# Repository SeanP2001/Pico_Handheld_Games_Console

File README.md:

# Pico Handheld Games Console

## Table of Contents

* [Introduction](#introduction)
* [Brief](#brief)
* [Circuitry](#circuitry)
  + [Schematic](#schematic)
  + [PCB Design](#pcb-design)
  + [Display Pinout Jumpers](#display-pinout-jumpers)
  + [Soldered PCB](#soldered-pcb)
* [Board Manager & Programming Setup](#board-manager---programming-setup)
* [Code](#code)
* [Enclosure](#enclosure)
  + [CAD Renders](#cad-renders)
  + [3D Printed and Assembled](#3d-printed-and-assembled)
* [Game Library](#game-library)
* [Further Work](#further-work)

## Introduction

I started this project to follow on from my [ATtiny Handheld Games Console](https://github.com/SeanP2001/ATtiny_Handheld_Games_Console). I decided the project was not as accessible as I wanted because programming an ATtiny is not simple enough for a beginner. While the limitations of the ATtiny make it a fun challenge to create games, it would be nice to be able to make something more elaborate.

## Brief

I wanted to make a USB-programmable games console which could be programmed using either MicroPython or C++ (Arduino). I also wanted to use silicone button membranes to give the buttons a more premium feel compared to the tactile buttons on the ATtiny console. I also decided to make a version with a colour LCD display (see the ["LCD_Version"](https://github.com/SeanP2001/Pico_Handheld_Games_Console/tree/LCD_Version) branch).

## Circuitry

### Schematic

### PCB Design

|  |  |
| ------------------------------------ | ----------------------------------- |

### Display Pinout Jumpers

A feature of the PCB is the jumper connections under the display. The I2C OLED displays do not all have the same pin layout. When you buy a display online, the item you receive may not have the same pinout as the one in the photos. Due to this inconsistency, I designed the board to work with both pinouts. If your display has the pinout (in order) Vcc/GND/SCL/SDA then you need to use solder to bridge the middle pads to the upper pads (shown in blue below). If it is GND/Vcc/SCL/SDA then you need to bridge the middle pads to the lower pads (shown in red below). Once you have done this, use Kapton tape to insulate the solder bridges and prevent them from causing a short circuit on the back of the display.

|  |  |
| --------------------------------------------------- | ----------------------------------------------------------------- |

### Soldered PCB

## Board Manager & Programming Setup

To program the board in the Arduino IDE, I used the [arduino-pico](https://github.com/earlephilhower/arduino-pico) board manager. I installed this using the method shown in the arduino-pico repository.

For programming the Pico using MicroPython, I followed the fantastic [Official Raspberry Pi Foundation Documentation](https://projects.raspberrypi.org/en/projects/getting-started-with-the-pico). Before this project, I had never used MicroPython, and the information provided was very helpful.

## Code

This repository includes code to test that the buttons, buzzer and display are working correctly. There are two versions; one is an Arduino sketch, and the other is written in MicroPython. When you press a button, the buzzer will sound, and the display will show the name of the button pressed. Recognised buttons are as follows:

- UP
- DOWN
- LEFT
- RIGHT
- A
- B

## Enclosure

### CAD Renders

|  |  |
| --------------------------------------- | --------------------------------------- |

### 3D Printed and Assembled

|  |  |
| ------------------------------------------- | ------------------------------------------ |
|      |   |

## Game Library

Currently, there are no games for the Pico Handheld Games Console. If you make any games for this console, please do a "fork and pull request" to add a link to the repository for your game in this section.

## Further Work

This project has achieved its goal of being a more accessible, USB-programmable alternative to my [ATtiny Handheld Games Console](https://github.com/SeanP2001/ATtiny_Handheld_Games_Console).

In future, I would like to push this concept further to make a more advanced console with a larger, colour LCD. I am researching suitable LCDs which can be driven by the Pico (with a frame buffer). To follow the development of this version of the project, please see the ["LCD_Version"](https://github.com/SeanP2001/Pico_Handheld_Games_Console/tree/LCD_Version) branch.

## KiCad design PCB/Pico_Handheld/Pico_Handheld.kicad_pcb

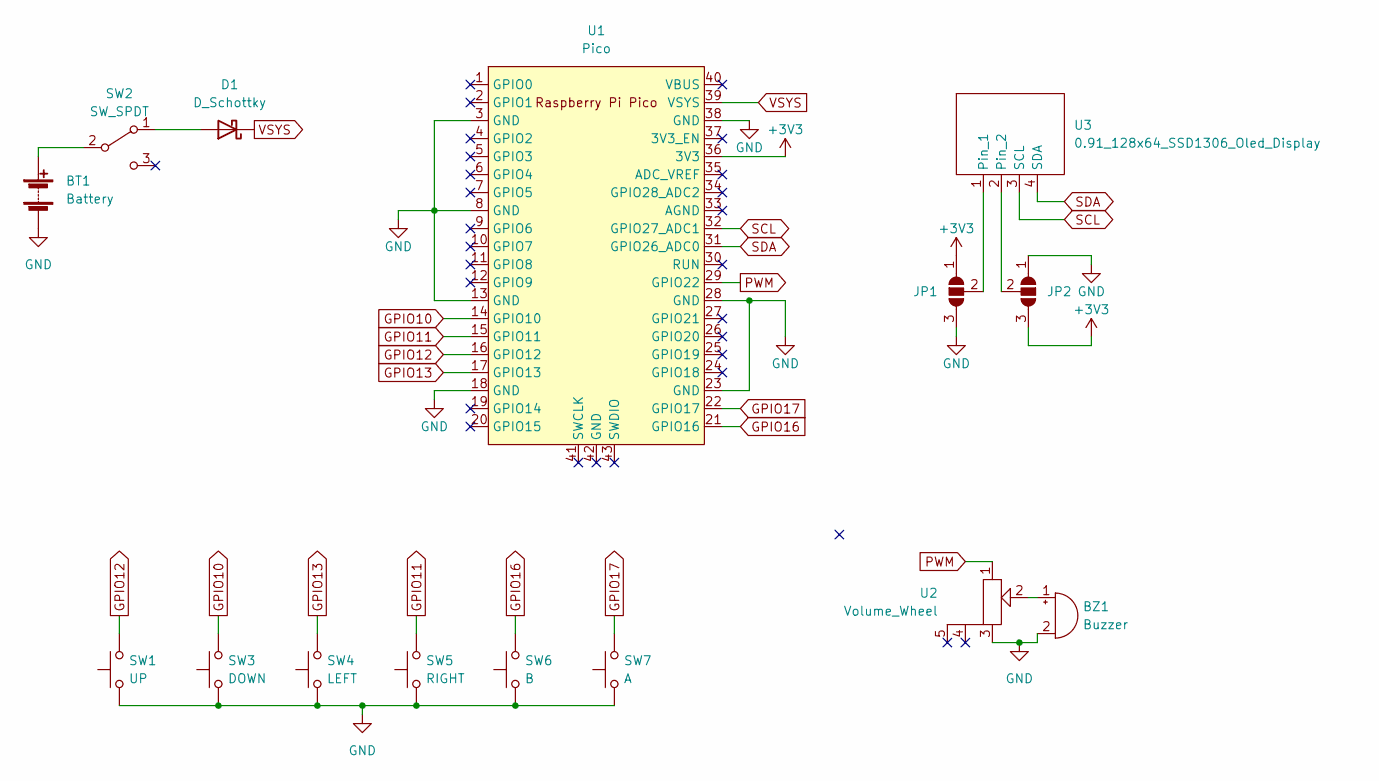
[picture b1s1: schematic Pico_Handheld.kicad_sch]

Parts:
BT1: Battery; 3xAA_Battery_Holder
BZ1: Buzzer; MagneticBuzzer_ProSignal_ABT-410-RC
D1: D_Schottky; D_A-405_P7.62mm_Horizontal
JP1, JP2: SolderJumper_3_Open; SolderJumper-3_P1.3mm_Open_Pad1.0x1.5mm
SW1: UP; Silicone_Button_Pad
SW2: SW_SPDT; SW_Slide_1P2T_CK_OS102011MS2Q
SW3: DOWN; Silicone_Button_Pad
SW4: LEFT; Silicone_Button_Pad
SW5: RIGHT; Silicone_Button_Pad
SW6: B; Silicone_Button_Pad
SW7: A; Silicone_Button_Pad
U1: Pico; RPi_Pico_SMD_TH
U2: Volume_Wheel
U3: 0.91_128x64_SSD1306_Oled_Display

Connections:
+3V3: JP1.1 (A), JP2.3 (B), U1.36 (3V3)
GND: BT1.2 (-), BZ1.2 (+), JP1.3 (B), JP2.1 (A), SW1.1, SW3.1, SW4.1, SW5.1, SW6.1, SW7.1, U1.3 (GND), U1.8 (GND), U1.13 (GND), U1.18 (GND), U1.23 (GND), U1.28 (GND), U1.38 (GND), U2.3
GPIO10: SW3.2, U1.14 (GPIO10)
GPIO11: SW5.2, U1.15 (GPIO11)
GPIO12: SW1.2, U1.16 (GPIO12)
GPIO13: SW4.2, U1.17 (GPIO13)
GPIO16: SW6.2, U1.21 (GPIO16)
GPIO17: SW7.2, U1.22 (GPIO17)
unnamed: BT1.1 (+), SW2.2 (B)
unnamed: BZ1.1 (-), U2.2
unnamed: D1.2 (A), SW2.1 (A)
unnamed: JP1.2 (C), U3.1
unnamed: JP2.2 (C), U3.2
PWM: U1.29 (GPIO22), U2.1
SCL: U1.32 (GPIO27_ADC1), U3.3 (SCL)
SDA: U1.31 (GPIO26_ADC0), U3.4 (SDA)
VSYS: D1.1 (K), U1.39 (VSYS)

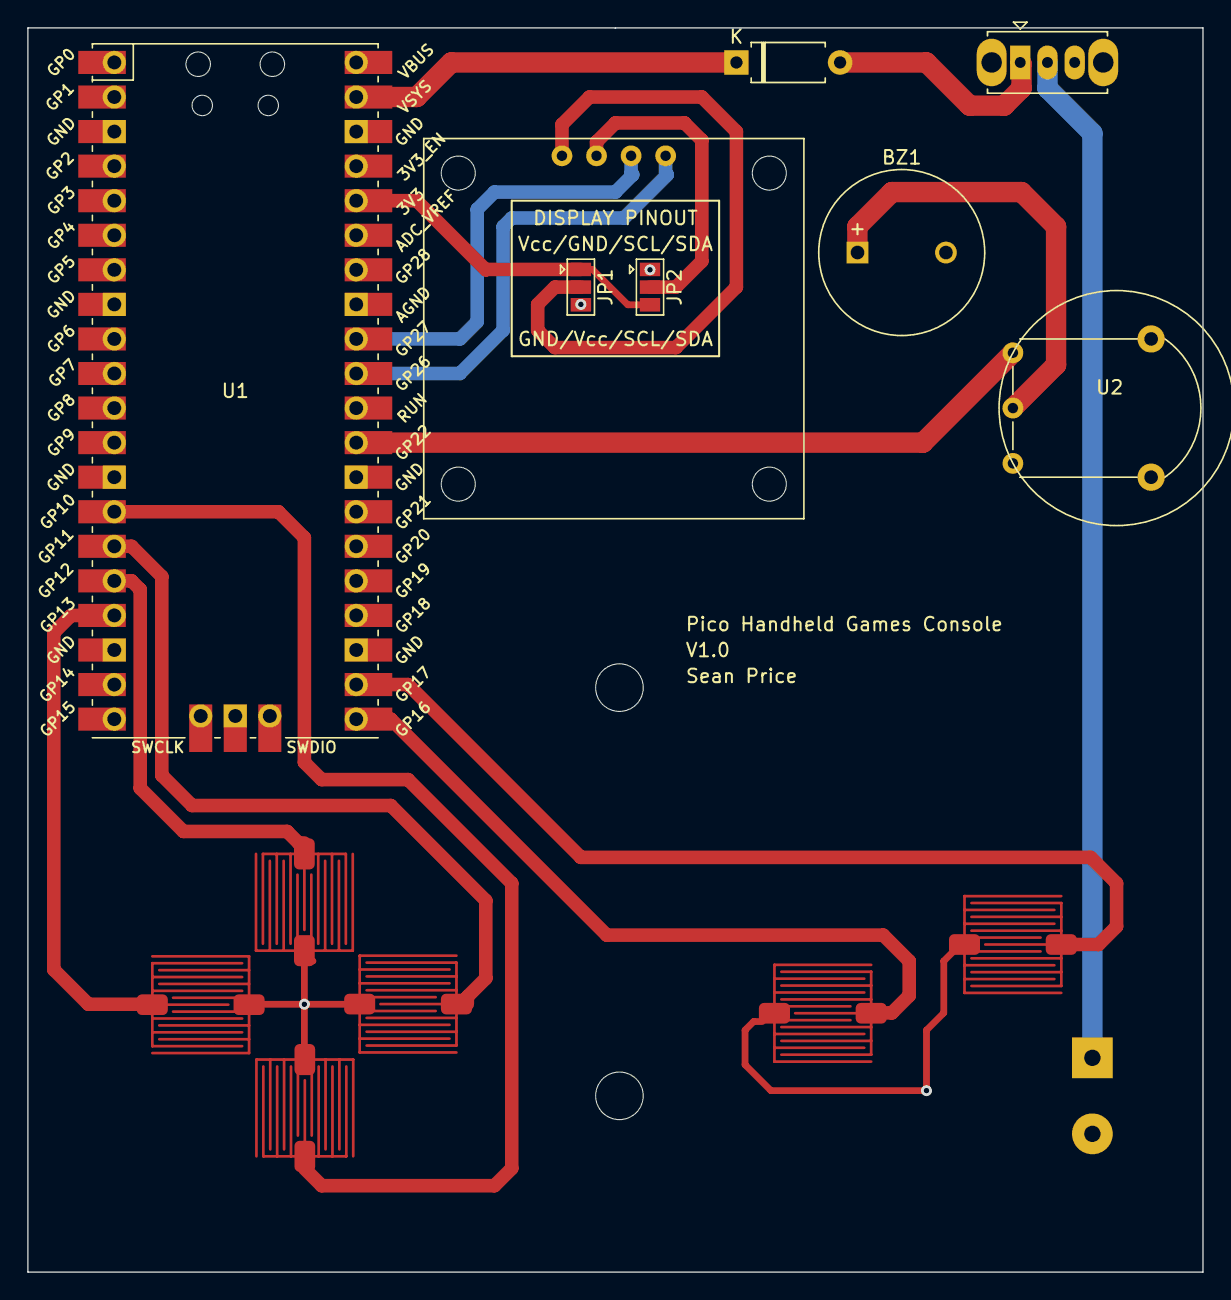
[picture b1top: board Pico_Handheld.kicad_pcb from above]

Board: 2 copper layers, 86.4 x 91.4 mm, 15 parts (1 on the bottom side), 17 nets.

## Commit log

2022-06-02 V0.1.0 Designed PCB
2022-06-07 V0.1.1 Finalised PCB V1.0
2022-09-14 V0.1.2 Added LICENSE.md
2022-09-23 V0.1.3 Updated README.md
2022-09-26 V0.2.0 Updated Schematic to Use an ILI9341 TFT LCD
2022-09-26 V0.3.0 Added MicroPython ButtonTest with ILI9341 Display
2022-09-26 V0.4.0 Added C++ ButtonTest and ColourTest with ILI9341 Display
2022-09-26 V0.5.0 Added MicroPython ColourSelector and ColourTest
2022-09-26 V0.5.1 Updated C++ ColourTest and Added DARK_GREEN to Colours.h
    Now the background colour changes instead of the text colour.
2022-09-26 V0.5.2 Updated MicroPython ColourTest and Added Libraries
    The MicroPython ColourTest now has a shorter 4 second delay between changing colours.
    I added a the Code>MicroPython>Libraries directory to store the zip files for any libraries which the MicroPython code uses.
2022-10-23 V0.6.0 Created C++ Moving Character Demo
2022-10-24 V0.6.1 Made The Jump Arc Less Linear
2023-01-22 V0.7.0 CAD Modelled Enclosure (For OLED Version)
2023-01-28 V0.7.1 3D Printed Enclosure and Assembled Console
2023-01-28 V0.7.2 Split PCB Designs into OLED and LCD Variants
2023-01-28 V0.8.0 Wrote Code to Test the OLED Variant Hardware (C++ & MicroPython)
2023-01-28 Created LCD_Version Branch
2023-01-28 V8.0.1 Removed the LCD Variant from the OLED Branch
2023-01-29 V1.0.0 Updated README.md
2023-01-29 V1.0.1 Updated README.md
